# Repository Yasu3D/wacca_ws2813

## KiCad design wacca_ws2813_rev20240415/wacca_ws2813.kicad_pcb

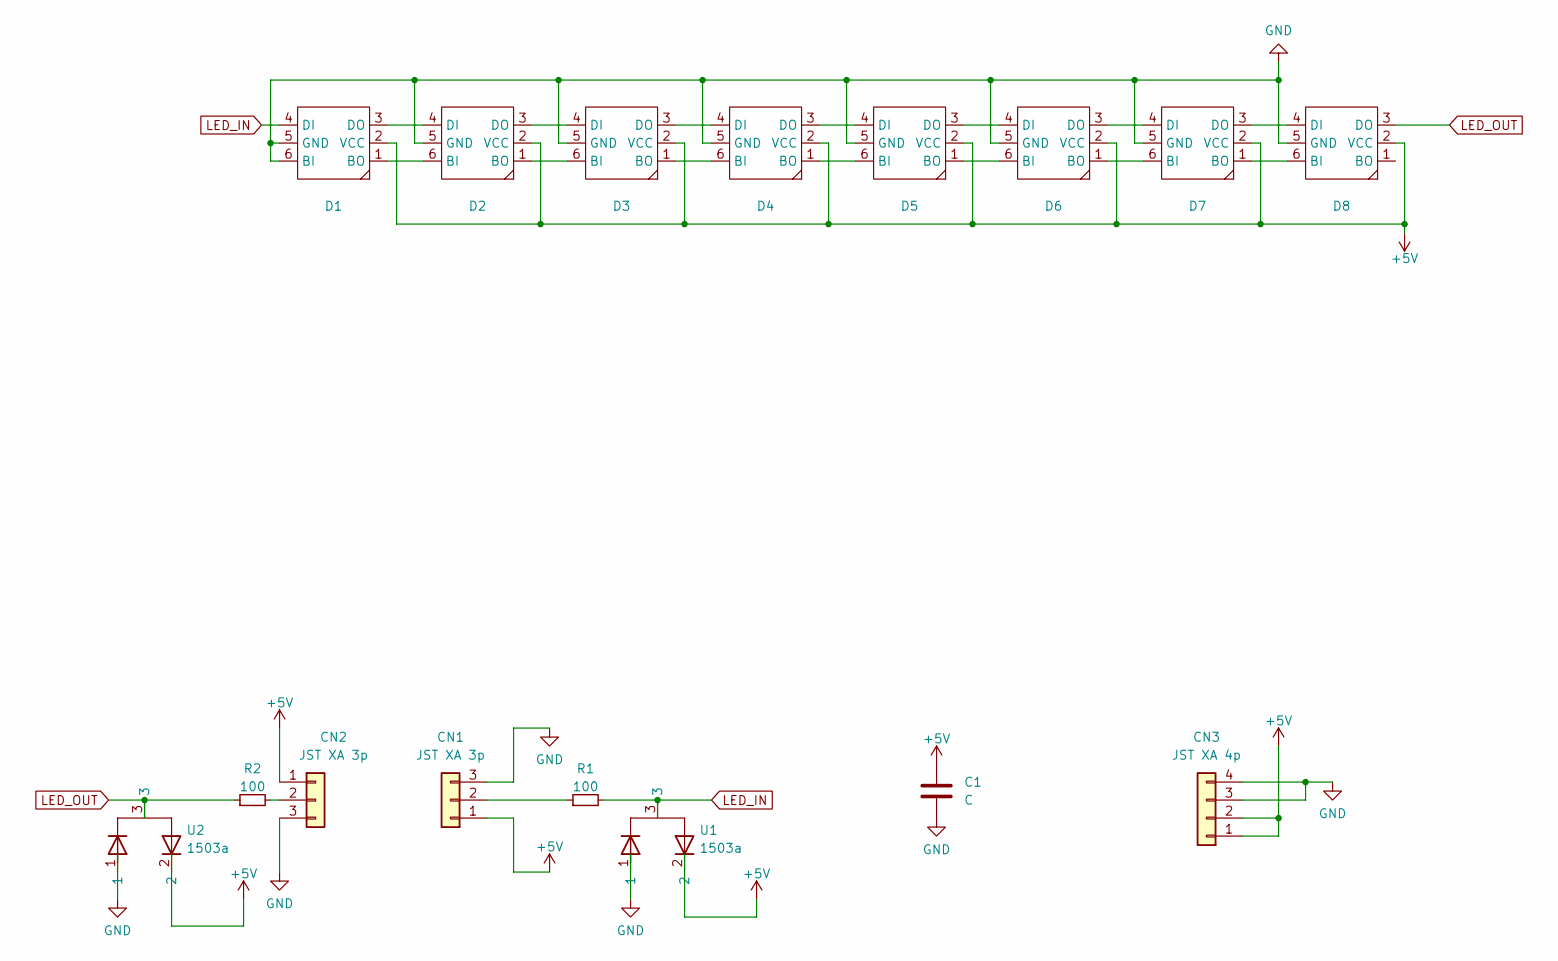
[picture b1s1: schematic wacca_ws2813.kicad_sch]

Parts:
C1: C; CP_EIA-7343-31_Kemet-D
CN1, CN2: JST XA 3p; JST_XA_B03B-XASK-1_1x03_P2.50mm_Vertical
CN3: JST XA 4p; JST_XA_B04B-XASK-1_1x04_P2.50mm_Vertical
D1, D2, D3, D4, D5, D6, D7, D8: LED_WS2812_PLCC6_5.0x5.0mm_P1.6mm
R1, R2: 100; R_0805_2012Metric_Pad1.20x1.40mm_HandSolder
U1, U2: 1503a; TSOT-23_HandSoldering

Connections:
+5V: C1.1, CN1.1, CN2.1, CN3.1, CN3.2, D1.2 (VCC), D2.2 (VCC), D3.2 (VCC), D4.2 (VCC), D5.2 (VCC), D6.2 (VCC), D7.2 (VCC), D8.2 (VCC), U1.2, U2.2
GND: C1.2, CN1.3, CN2.3, CN3.3, CN3.4, D1.5 (GND), D1.6 (BI), D2.5 (GND), D3.5 (GND), D4.5 (GND), D5.5 (GND), D6.5 (GND), D7.5 (GND), D8.5 (GND), U1.1, U2.1
LED_IN: D1.4 (DI), R1.2, U1.3
LED_OUT: D8.3 (DO), R2.1, U2.3
unnamed: CN1.2, R1.1
unnamed: CN2.2, R2.2
unnamed: D1.1 (BO), D2.6 (BI)
unnamed: D1.3 (DO), D2.4 (DI)
unnamed: D2.1 (BO), D3.6 (BI)
unnamed: D2.3 (DO), D3.4 (DI)
unnamed: D3.1 (BO), D4.6 (BI)
unnamed: D3.3 (DO), D4.4 (DI)
unnamed: D4.1 (BO), D5.6 (BI)
unnamed: D4.3 (DO), D5.4 (DI)
unnamed: D5.1 (BO), D6.6 (BI)
unnamed: D5.3 (DO), D6.4 (DI)
unnamed: D6.1 (BO), D7.6 (BI)
unnamed: D6.3 (DO), D7.4 (DI)
unnamed: D7.1 (BO), D8.6 (BI)
unnamed: D7.3 (DO), D8.4 (DI)

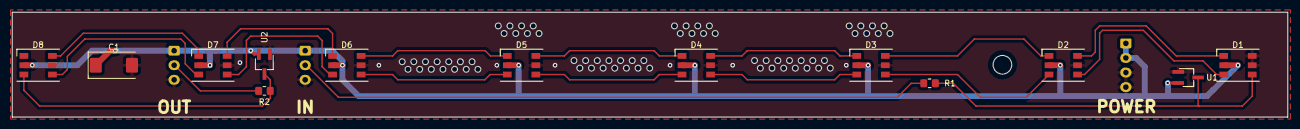
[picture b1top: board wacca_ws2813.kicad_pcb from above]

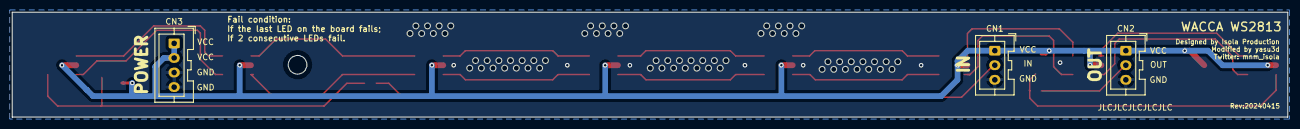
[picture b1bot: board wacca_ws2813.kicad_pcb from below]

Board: 2 copper layers, 219.0 x 18.0 mm, 16 parts (3 on the bottom side), 20 nets.

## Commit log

2024-04-15 new revision
2024-04-15 Update revision date
2024-04-15 adjust position of holes a little
